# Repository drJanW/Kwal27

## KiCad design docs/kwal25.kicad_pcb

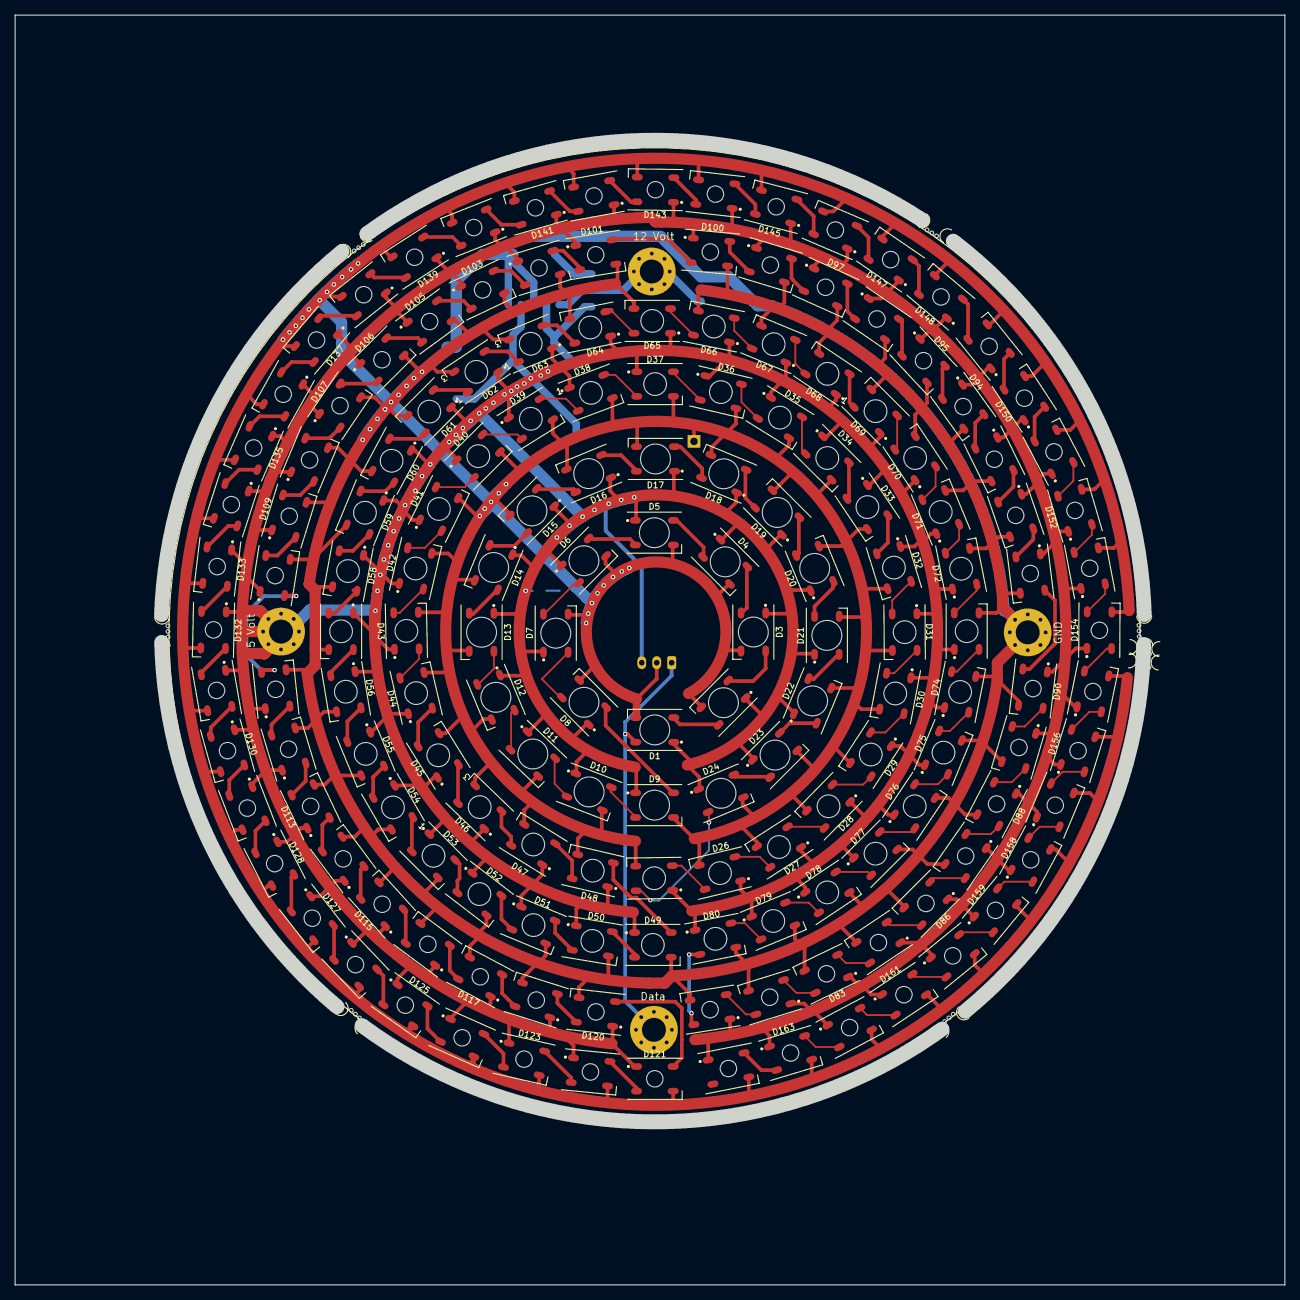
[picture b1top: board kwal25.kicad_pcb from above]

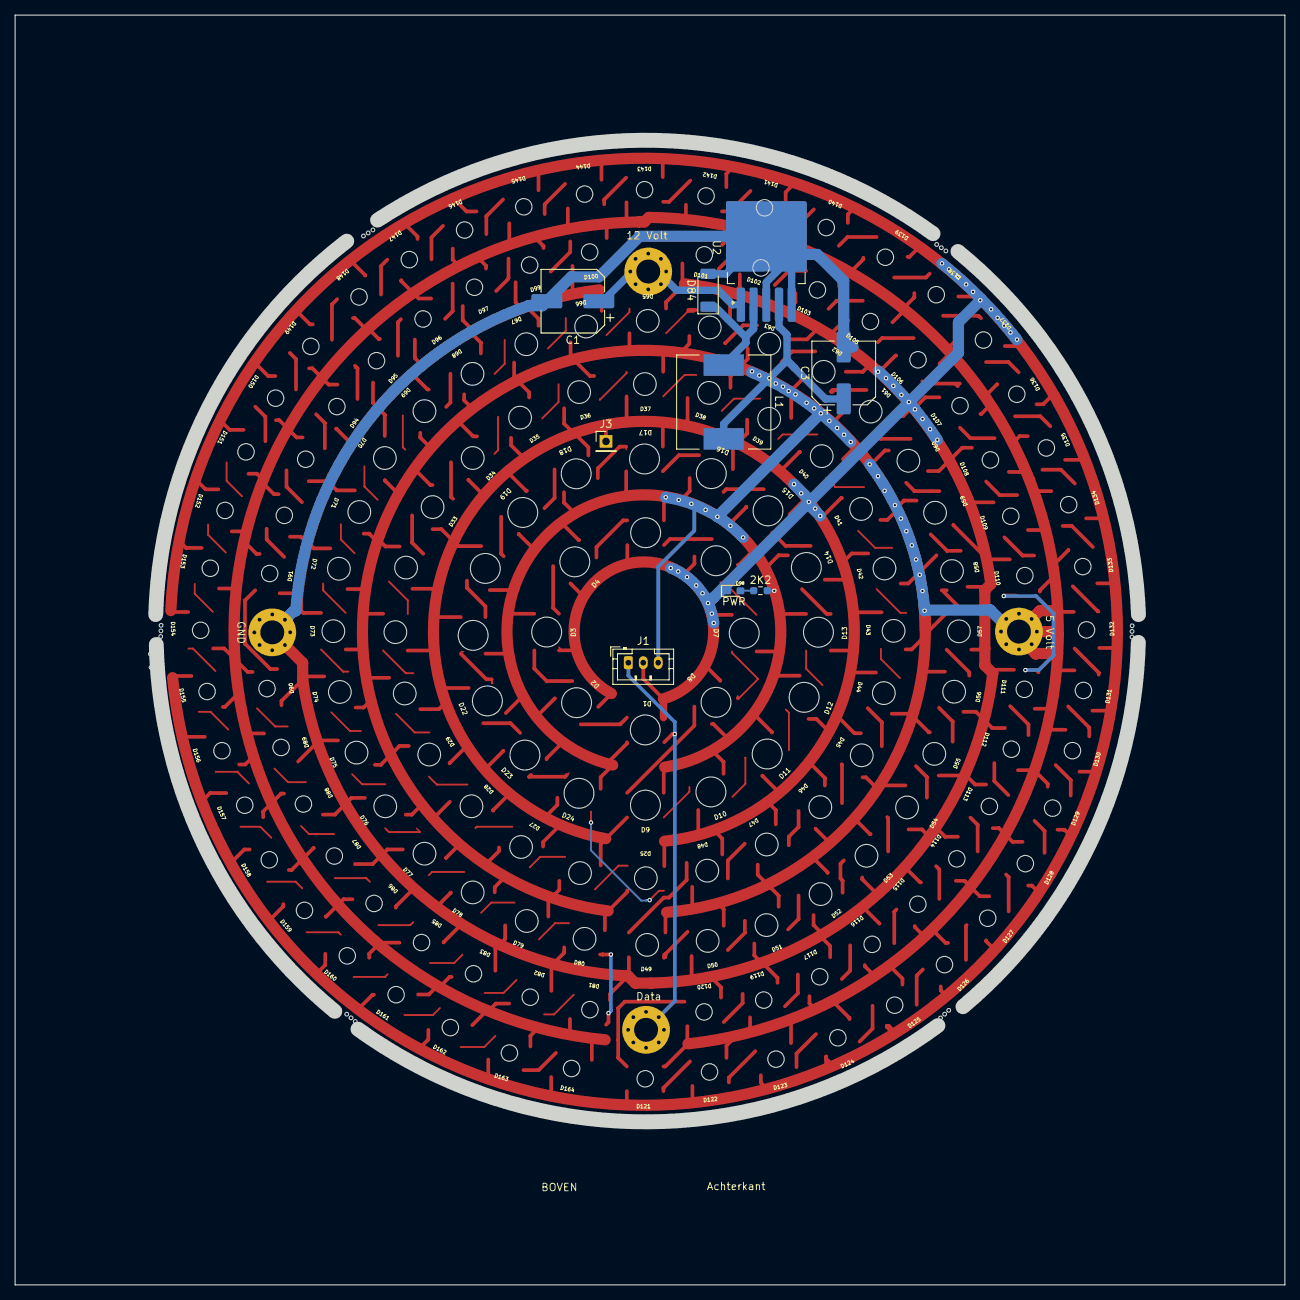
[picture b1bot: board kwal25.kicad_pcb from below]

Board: 2 copper layers, 170.0 x 170.0 mm, 181 parts (9 on the bottom side), 165 nets.

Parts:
C1: 100uF; CP_Elec_8x6.9
C3: 220 uF; CP_Elec_8x6.9
D1, D2, D3, D4, D5, D6, D7, D8, D9, D10, D11, D12, D13, D14, D15, D16, D17, D18, D19, D20, D21, D22, D23, D24: WS2812B; WS2812B_4_1
D25, D26, D27, D28, D29, D30, D31, D32, D33, D34, D35, D36, D37, D38, D39, D40, D41, D42, D43, D44, D45, D46, D47, D48, D49, D50, D51, D52, D53, D54, D55, D56, D57, D58, D59, D60, D61, D62, D63, D64, D65, D66, D67, D68, D69, D70, D71, D72, D73, D74, D75, D76, D77, D78, D79, D80: WS2812B; WS2812B_3_1
D81, D82, D83, D85, D86, D87, D88, D89, D90, D91, D92, D93, D94, D95, D96, D97, D99, D100, D101, D102, D103, D105, D106, D107, D108, D109, D110, D111, D112, D113, D114, D115, D116, D117, D119, D120, D121, D122, D123, D124, D125, D126, D127, D128, D129, D130, D131, D132, D133, D134, D135, D136, D137, D138, D139, D140, D141, D142, D143, D144, D145, D146, D147, D148, D149, D150, D151, D152, D153, D154, D155, D156, D157, D158, D159, D160, D161, D162, D163, D164: WS2812B; WS2812B_2_1
D84: SS34; D_SOD-128
D98: PWR; LED_0603_1608Metric_Pad1.05x0.95mm_HandSolder
H1: 12V; MountingHole_3.2mm_M3_Pad_Via
H2: Data; MountingHole_3.2mm_M3_Pad_Via
H3: Gnd; MountingHole_3.2mm_M3_Pad_Via
H4: 5V; MountingHole_3.2mm_M3_Pad_Via
J1: Conn_01x03; JST_PH_B3B-PH-K_1x03_P2.00mm_Vertical
J3: GND; PinHeader_1x01_P2.54mm_Vertical
L1: 470; L_12x12mm_H8mm
R1: 2K2; R_0603_1608Metric_Pad0.98x0.95mm_HandSolder
U2: LM2596S-5; TO-263-5_TabPin3
mouse-bite-1, mouse-bite-1#2, mouse-bite-1#3, mouse-bite-1#4, mouse-bite-1#5, mouse-bite-1#6, mouse-bite-1#7, mouse-bite-1#8: VAL**; mouse-bite-single-2mm-slot

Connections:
+5V: C3.1, D1.1 (VDD), D2.1 (VDD), D3.1 (VDD), D4.1 (VDD), D5.1 (VDD), D6.1 (VDD), D7.1 (VDD), D8.1 (VDD), D9.1 (VDD), D10.1 (VDD), D11.1 (VDD), D12.1 (VDD), D13.1 (VDD), D14.1 (VDD), D15.1 (VDD), D16.1 (VDD), D17.1 (VDD), D18.1 (VDD), D19.1 (VDD), D20.1 (VDD), D21.1 (VDD), D22.1 (VDD), D23.1 (VDD), D24.1 (VDD), D25.1 (VDD), D26.1 (VDD), D27.1 (VDD), D28.1 (VDD), D29.1 (VDD), D30.1 (VDD), D31.1 (VDD), D32.1 (VDD), D33.1 (VDD), D34.1 (VDD), D35.1 (VDD), D36.1 (VDD), D37.1 (VDD), D38.1 (VDD), D39.1 (VDD), D40.1 (VDD), D41.1 (VDD), D42.1 (VDD), D43.1 (VDD), D44.1 (VDD), D45.1 (VDD), D46.1 (VDD), D47.1 (VDD), D48.1 (VDD), D49.1 (VDD), D50.1 (VDD), D51.1 (VDD), D52.1 (VDD), D53.1 (VDD), D54.1 (VDD), D55.1 (VDD), D56.1 (VDD), D57.1 (VDD), D58.1 (VDD), D59.1 (VDD), D60.1 (VDD), D61.1 (VDD), D62.1 (VDD), D63.1 (VDD), D64.1 (VDD), D65.1 (VDD), D66.1 (VDD), D67.1 (VDD), D68.1 (VDD), D69.1 (VDD), D70.1 (VDD), D71.1 (VDD), D72.1 (VDD), D73.1 (VDD), D74.1 (VDD), D75.1 (VDD), D76.1 (VDD), D77.1 (VDD), D78.1 (VDD), D79.1 (VDD), D80.1 (VDD), D81.1 (VDD), D82.1 (VDD), D83.1 (VDD), D85.1 (VDD), D86.1 (VDD), D87.1 (VDD), D88.1 (VDD), D89.1 (VDD), D90.1 (VDD), D91.1 (VDD), D92.1 (VDD), D93.1 (VDD), D94.1 (VDD), D95.1 (VDD), D96.1 (VDD), D97.1 (VDD), D99.1 (VDD), D100.1 (VDD), D101.1 (VDD), D102.1 (VDD), D103.1 (VDD), D105.1 (VDD), D106.1 (VDD), D107.1 (VDD), D108.1 (VDD), D109.1 (VDD), D110.1 (VDD), D111.1 (VDD), D112.1 (VDD), D113.1 (VDD), D114.1 (VDD), D115.1 (VDD), D116.1 (VDD), D117.1 (VDD), D119.1 (VDD), D120.1 (VDD), D121.1 (VDD), D122.1 (VDD), D123.1 (VDD), D124.1 (VDD), D125.1 (VDD), D126.1 (VDD), D127.1 (VDD), D128.1 (VDD), D129.1 (VDD), D130.1 (VDD), D131.1 (VDD), D132.1 (VDD), D133.1 (VDD), D134.1 (VDD), D135.1 (VDD), D136.1 (VDD), D137.1 (VDD), D138.1 (VDD), D139.1 (VDD), D140.1 (VDD), D141.1 (VDD), D142.1 (VDD), D143.1 (VDD), D144.1 (VDD), D145.1 (VDD), D146.1 (VDD), D147.1 (VDD), D148.1 (VDD), D149.1 (VDD), D150.1 (VDD), D151.1 (VDD), D152.1 (VDD), D153.1 (VDD), D154.1 (VDD), D155.1 (VDD), D156.1 (VDD), D157.1 (VDD), D158.1 (VDD), D159.1 (VDD), D160.1 (VDD), D161.1 (VDD), D162.1 (VDD), D163.1 (VDD), D164.1 (VDD), H4.1, J1.3, L1.2, R1.1, U2.4 (FB)
+12V: C1.1, H1.1, U2.1 (VIN)
Data: D1.4 (DIN), H2.1, J1.1
GND: C1.2, C3.2, D1.3 (VSS), D2.3 (VSS), D3.3 (VSS), D4.3 (VSS), D5.3 (VSS), D6.3 (VSS), D7.3 (VSS), D8.3 (VSS), D9.3 (VSS), D10.3 (VSS), D11.3 (VSS), D12.3 (VSS), D13.3 (VSS), D14.3 (VSS), D15.3 (VSS), D16.3 (VSS), D17.3 (VSS), D18.3 (VSS), D19.3 (VSS), D20.3 (VSS), D21.3 (VSS), D22.3 (VSS), D23.3 (VSS), D24.3 (VSS), D25.3 (VSS), D26.3 (VSS), D27.3 (VSS), D28.3 (VSS), D29.3 (VSS), D30.3 (VSS), D31.3 (VSS), D32.3 (VSS), D33.3 (VSS), D34.3 (VSS), D35.3 (VSS), D36.3 (VSS), D37.3 (VSS), D38.3 (VSS), D39.3 (VSS), D40.3 (VSS), D41.3 (VSS), D42.3 (VSS), D43.3 (VSS), D44.3 (VSS), D45.3 (VSS), D46.3 (VSS), D47.3 (VSS), D48.3 (VSS), D49.3 (VSS), D50.3 (VSS), D51.3 (VSS), D52.3 (VSS), D53.3 (VSS), D54.3 (VSS), D55.3 (VSS), D56.3 (VSS), D57.3 (VSS), D58.3 (VSS), D59.3 (VSS), D60.3 (VSS), D61.3 (VSS), D62.3 (VSS), D63.3 (VSS), D64.3 (VSS), D65.3 (VSS), D66.3 (VSS), D67.3 (VSS), D68.3 (VSS), D69.3 (VSS), D70.3 (VSS), D71.3 (VSS), D72.3 (VSS), D73.3 (VSS), D74.3 (VSS), D75.3 (VSS), D76.3 (VSS), D77.3 (VSS), D78.3 (VSS), D79.3 (VSS), D80.3 (VSS), D81.3 (VSS), D82.3 (VSS), D83.3 (VSS), D84.2 (A), D85.3 (VSS), D86.3 (VSS), D87.3 (VSS), D88.3 (VSS), D89.3 (VSS), D90.3 (VSS), D91.3 (VSS), D92.3 (VSS), D93.3 (VSS), D94.3 (VSS), D95.3 (VSS), D96.3 (VSS), D97.3 (VSS), D98.1 (K), D99.3 (VSS), D100.3 (VSS), D101.3 (VSS), D102.3 (VSS), D103.3 (VSS), D105.3 (VSS), D106.3 (VSS), D107.3 (VSS), D108.3 (VSS), D109.3 (VSS), D110.3 (VSS), D111.3 (VSS), D112.3 (VSS), D113.3 (VSS), D114.3 (VSS), D115.3 (VSS), D116.3 (VSS), D117.3 (VSS), D119.3 (VSS), D120.3 (VSS), D121.3 (VSS), D122.3 (VSS), D123.3 (VSS), D124.3 (VSS), D125.3 (VSS), D126.3 (VSS), D127.3 (VSS), D128.3 (VSS), D129.3 (VSS), D130.3 (VSS), D131.3 (VSS), D132.3 (VSS), D133.3 (VSS), D134.3 (VSS), D135.3 (VSS), D136.3 (VSS), D137.3 (VSS), D138.3 (VSS), D139.3 (VSS), D140.3 (VSS), D141.3 (VSS), D142.3 (VSS), D143.3 (VSS), D144.3 (VSS), D145.3 (VSS), D146.3 (VSS), D147.3 (VSS), D148.3 (VSS), D149.3 (VSS), D150.3 (VSS), D151.3 (VSS), D152.3 (VSS), D153.3 (VSS), D154.3 (VSS), D155.3 (VSS), D156.3 (VSS), D157.3 (VSS), D158.3 (VSS), D159.3 (VSS), D160.3 (VSS), D161.3 (VSS), D162.3 (VSS), D163.3 (VSS), D164.3 (VSS), H3.1, J1.2, J3.1, U2.3 (GND), U2.5 (~ON/OFF)
unnamed: D1.2 (DOUT), D2.4 (DIN)
unnamed: D2.2 (DOUT), D3.4 (DIN)
unnamed: D3.2 (DOUT), D4.4 (DIN)
unnamed: D4.2 (DOUT), D5.4 (DIN)
unnamed: D5.2 (DOUT), D6.4 (DIN)
unnamed: D6.2 (DOUT), D7.4 (DIN)
unnamed: D7.2 (DOUT), D8.4 (DIN)
unnamed: D8.2 (DOUT), D9.4 (DIN)
unnamed: D9.2 (DOUT), D10.4 (DIN)
unnamed: D10.2 (DOUT), D11.4 (DIN)
unnamed: D11.2 (DOUT), D12.4 (DIN)
unnamed: D12.2 (DOUT), D13.4 (DIN)
unnamed: D13.2 (DOUT), D14.4 (DIN)
unnamed: D14.2 (DOUT), D15.4 (DIN)
unnamed: D15.2 (DOUT), D16.4 (DIN)
unnamed: D16.2 (DOUT), D17.4 (DIN)
unnamed: D17.2 (DOUT), D18.4 (DIN)
unnamed: D18.2 (DOUT), D19.4 (DIN)
unnamed: D19.2 (DOUT), D20.4 (DIN)
unnamed: D20.2 (DOUT), D21.4 (DIN)
unnamed: D21.2 (DOUT), D22.4 (DIN)
unnamed: D22.2 (DOUT), D23.4 (DIN)
unnamed: D23.2 (DOUT), D24.4 (DIN)
unnamed: D24.2 (DOUT), D25.4 (DIN)
unnamed: D25.2 (DOUT), D26.4 (DIN)
unnamed: D26.2 (DOUT), D27.4 (DIN)
unnamed: D27.2 (DOUT), D28.4 (DIN)
unnamed: D28.2 (DOUT), D29.4 (DIN)
unnamed: D29.2 (DOUT), D30.4 (DIN)
unnamed: D30.2 (DOUT), D31.4 (DIN)
unnamed: D31.2 (DOUT), D32.4 (DIN)
unnamed: D32.2 (DOUT), D33.4 (DIN)
unnamed: D33.2 (DOUT), D34.4 (DIN)
unnamed: D34.2 (DOUT), D35.4 (DIN)
unnamed: D35.2 (DOUT), D36.4 (DIN)
unnamed: D36.2 (DOUT), D37.4 (DIN)
unnamed: D37.2 (DOUT), D38.4 (DIN)
unnamed: D38.2 (DOUT), D39.4 (DIN)
unnamed: D39.2 (DOUT), D40.4 (DIN)
unnamed: D40.2 (DOUT), D41.4 (DIN)
unnamed: D41.2 (DOUT), D42.4 (DIN)
unnamed: D42.2 (DOUT), D43.4 (DIN)
unnamed: D43.2 (DOUT), D44.4 (DIN)
unnamed: D44.2 (DOUT), D45.4 (DIN)
unnamed: D45.2 (DOUT), D46.4 (DIN)
unnamed: D46.2 (DOUT), D47.4 (DIN)
unnamed: D47.2 (DOUT), D48.4 (DIN)
unnamed: D48.2 (DOUT), D49.4 (DIN)
unnamed: D49.2 (DOUT), D50.4 (DIN)
unnamed: D50.2 (DOUT), D51.4 (DIN)
unnamed: D51.2 (DOUT), D52.4 (DIN)
unnamed: D52.2 (DOUT), D53.4 (DIN)
unnamed: D53.2 (DOUT), D54.4 (DIN)
unnamed: D54.2 (DOUT), D55.4 (DIN)
unnamed: D55.2 (DOUT), D56.4 (DIN)
unnamed: D56.2 (DOUT), D57.4 (DIN)
unnamed: D57.2 (DOUT), D58.4 (DIN)
unnamed: D58.2 (DOUT), D59.4 (DIN)
unnamed: D59.2 (DOUT), D60.4 (DIN)
unnamed: D60.2 (DOUT), D61.4 (DIN)
unnamed: D61.2 (DOUT), D62.4 (DIN)
unnamed: D62.2 (DOUT), D63.4 (DIN)
unnamed: D63.2 (DOUT), D64.4 (DIN)
unnamed: D64.2 (DOUT), D65.4 (DIN)
unnamed: D65.2 (DOUT), D66.4 (DIN)
unnamed: D66.2 (DOUT), D67.4 (DIN)
unnamed: D67.2 (DOUT), D68.4 (DIN)
unnamed: D68.2 (DOUT), D69.4 (DIN)
unnamed: D69.2 (DOUT), D70.4 (DIN)
unnamed: D70.2 (DOUT), D71.4 (DIN)
unnamed: D71.2 (DOUT), D72.4 (DIN)
unnamed: D72.2 (DOUT), D73.4 (DIN)
unnamed: D73.2 (DOUT), D74.4 (DIN)
unnamed: D74.2 (DOUT), D75.4 (DIN)
unnamed: D75.2 (DOUT), D76.4 (DIN)
unnamed: D76.2 (DOUT), D77.4 (DIN)
unnamed: D77.2 (DOUT), D78.4 (DIN)
unnamed: D78.2 (DOUT), D79.4 (DIN)
unnamed: D79.2 (DOUT), D80.4 (DIN)
unnamed: D80.2 (DOUT), D81.4 (DIN)
unnamed: D81.2 (DOUT), D82.4 (DIN)
unnamed: D82.2 (DOUT), D83.4 (DIN)
unnamed: D83.2 (DOUT), D85.4 (DIN)
unnamed: D84.1 (K), L1.1, U2.2 (OUT)
unnamed: D85.2 (DOUT), D86.4 (DIN)
unnamed: D86.2 (DOUT), D87.4 (DIN)
unnamed: D87.2 (DOUT), D88.4 (DIN)
unnamed: D88.2 (DOUT), D89.4 (DIN)
unnamed: D89.2 (DOUT), D90.4 (DIN)
unnamed: D90.2 (DOUT), D91.4 (DIN)
unnamed: D91.2 (DOUT), D92.4 (DIN)
unnamed: D92.2 (DOUT), D93.4 (DIN)
unnamed: D93.2 (DOUT), D94.4 (DIN)
unnamed: D94.2 (DOUT), D95.4 (DIN)
unnamed: D95.2 (DOUT), D96.4 (DIN)
unnamed: D96.2 (DOUT), D97.4 (DIN)
unnamed: D97.2 (DOUT), D99.4 (DIN)
unnamed: D98.2 (A), R1.2
unnamed: D99.2 (DOUT), D100.4 (DIN)
unnamed: D100.2 (DOUT), D101.4 (DIN)
unnamed: D101.2 (DOUT), D102.4 (DIN)
unnamed: D102.2 (DOUT), D103.4 (DIN)
unnamed: D103.2 (DOUT), D105.4 (DIN)
unnamed: D105.2 (DOUT), D106.4 (DIN)
unnamed: D106.2 (DOUT), D107.4 (DIN)
unnamed: D107.2 (DOUT), D108.4 (DIN)
unnamed: D108.2 (DOUT), D109.4 (DIN)
unnamed: D109.2 (DOUT), D110.4 (DIN)
unnamed: D110.2 (DOUT), D111.4 (DIN)
unnamed: D111.2 (DOUT), D112.4 (DIN)
unnamed: D112.2 (DOUT), D113.4 (DIN)
unnamed: D113.2 (DOUT), D114.4 (DIN)
unnamed: D114.2 (DOUT), D115.4 (DIN)
unnamed: D115.2 (DOUT), D116.4 (DIN)
unnamed: D116.2 (DOUT), D117.4 (DIN)
unnamed: D117.2 (DOUT), D119.4 (DIN)
unnamed: D119.2 (DOUT), D120.4 (DIN)
unnamed: D120.2 (DOUT), D121.4 (DIN)
unnamed: D121.2 (DOUT), D122.4 (DIN)
unnamed: D122.2 (DOUT), D123.4 (DIN)
unnamed: D123.2 (DOUT), D124.4 (DIN)
unnamed: D124.2 (DOUT), D125.4 (DIN)
unnamed: D125.2 (DOUT), D126.4 (DIN)
unnamed: D126.2 (DOUT), D127.4 (DIN)
unnamed: D127.2 (DOUT), D128.4 (DIN)
unnamed: D128.2 (DOUT), D129.4 (DIN)
unnamed: D129.2 (DOUT), D130.4 (DIN)
unnamed: D130.2 (DOUT), D131.4 (DIN)
unnamed: D131.2 (DOUT), D132.4 (DIN)
unnamed: D132.2 (DOUT), D133.4 (DIN)
unnamed: D133.2 (DOUT), D134.4 (DIN)
unnamed: D134.2 (DOUT), D135.4 (DIN)
unnamed: D135.2 (DOUT), D136.4 (DIN)
unnamed: D136.2 (DOUT), D137.4 (DIN)
unnamed: D137.2 (DOUT), D138.4 (DIN)
unnamed: D138.2 (DOUT), D139.4 (DIN)
unnamed: D139.2 (DOUT), D140.4 (DIN)
unnamed: D140.2 (DOUT), D141.4 (DIN)
unnamed: D141.2 (DOUT), D142.4 (DIN)
unnamed: D142.2 (DOUT), D143.4 (DIN)
unnamed: D143.2 (DOUT), D144.4 (DIN)
unnamed: D144.2 (DOUT), D145.4 (DIN)
unnamed: D145.2 (DOUT), D146.4 (DIN)
unnamed: D146.2 (DOUT), D147.4 (DIN)
unnamed: D147.2 (DOUT), D148.4 (DIN)
unnamed: D148.2 (DOUT), D149.4 (DIN)
unnamed: D149.2 (DOUT), D150.4 (DIN)
unnamed: D150.2 (DOUT), D151.4 (DIN)
unnamed: D151.2 (DOUT), D152.4 (DIN)
unnamed: D152.2 (DOUT), D153.4 (DIN)
unnamed: D153.2 (DOUT), D154.4 (DIN)
unnamed: D154.2 (DOUT), D155.4 (DIN)
unnamed: D155.2 (DOUT), D156.4 (DIN)
unnamed: D156.2 (DOUT), D157.4 (DIN)
unnamed: D157.2 (DOUT), D158.4 (DIN)
unnamed: D158.2 (DOUT), D159.4 (DIN)
unnamed: D159.2 (DOUT), D160.4 (DIN)
unnamed: D160.2 (DOUT), D161.4 (DIN)
unnamed: D161.2 (DOUT), D162.4 (DIN)
unnamed: D162.2 (DOUT), D163.4 (DIN)
unnamed: D163.2 (DOUT), D164.4 (DIN)

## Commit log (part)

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2026-01-27 260127A: baseline before TimerManager refactor (token support, global instance)
2026-01-27 260127A: timers global migration WIP
2026-01-27 260127A: TimerManager cleanup - T2,T4,T9 done
2026-01-28 SDManager refactor tested - 26/27 checks passed
2026-01-28 PRTClock: eliminate instance() singleton, use global prtClock
2026-01-29 LightManager: remove singleton, use global lightManager
2026-01-29 WiFiManager: remove status wrapper, align state access
2026-01-31 Clarify Copilot prompt and update rename todo
2026-01-31 Update rename todo and add v2 naming docs
2026-01-31 Light Store to Catalog/Table
2026-02-01 Docs: Store to Catalog/Table
2026-02-02 Rename: phase G terminology + calendar selector fix
2026-02-02 Cleanup: remove shim files
2026-02-02 Rename: manager folders to controller
2026-02-02 na renames
2026-02-04 NAS CSV server port 8081, nasstart.ps1 one-click
2026-02-05 Enable timestamps and update headers
2026-02-05 Rename BootMaster to BootManager for consistency
2026-02-06 Boot: welcome after calendar ready
2026-02-06 260206N: HTTP OTA upload, deploy.ps1 MARMER via HTTP, legacy OTA behouden
2026-02-07 260207D: b12 Stevens power law for lux brightness curve
2026-02-07 Move and rename AUDIO_GAIN_SEMANTICS.md -> docs/coding_tech/audio_volume_semantics.md
    - Renamed file: gain→volume in filename
    - Updated all prose: gain→volume, modifier→fraction
    - Updated getter/setter names to match current code (getVolumeShiftedHi, setVolumeWebShift)
    - Added note about pending variable renames (glossary cross-ref)
    - Version bumped to 260207F
2026-02-08 Custom canvas color picker - fixes Android WebView browsers (260208B)
    - New colorpicker.js: canvas-based HSV picker (touch + mouse)
    - colors.js: replace <input type=color> with custom picker
    - index.html: add colorpicker-modal (canvas, hue bar, hex input, preview)
    - styles.css: add .cp-* styles with touch-action:none
    - main.js: init Kwal.colorpicker before Kwal.colors
    - build.ps1: add colorpicker.js to module list
2026-02-09 260209B - Weather retry, health panel enhancements, speak temp guard
    - Weather fetch: two-phase boot retry (14x, 1.5× growth) then hourly periodic
    - Weather periodic failure: guard clearWeather() to preserve stale data
    - Health panel: show RTC temperature inline with RTC checkmark
    - Health panel: show calendar date (dd-mm) inline with Calendar checkmark
    - Speak temperature: limit to >75°C only, rename sayTemperature → sayRTCtemperature
    - Version bump: firmware + WebGUI 260209B
2026-02-10 color/pattern timer change: 5.8h color, 4.9h pattern, health log 40min
2026-02-11 260211B: fix OOM crash, add NAS health monitoring, timer-based voting
    Crash fix (OOM during audio+webserver):
    - WiFiBoot: defer NasBackup::checkHealth() to 30s one-shot timer
    (avoids 9th TCP connection while 8 CSV downloads still in TIME_WAIT)
    - LogBuffer: reduce 16KB -> 12KB (16KB was marginal with NasBackup TCP)
    NAS health monitoring (new SC_NAS status component):
    - AlertState: SC_NAS in enum, reset() inits NOT_OK, setNasStatus/isNasOk
2026-02-11 MP3 grid UX redesign + single-dir theme box + box name display
    MP3 Grid:
    - Remove header, replace play icon with close icon
    - Click DIR label/value: set single-dir theme box
    - Click FILE label/value: play that file
    - Double-click canvas: play file
    - Grid cell size 3 -> 5px, wrap height 300 -> 480px
2026-02-11 Make volume and brightness sliders linear (remove quadratic curve)
    - Removed Kwal.sliderToValue/valueToSlider calls from audio.js and brightness.js
    - Slider position now equals percentage directly
    - WebGUI 260211K, uploaded to both HOUT and MARMER
2026-02-12 260212D: rename getEffectiveVolume -> getVolumeMultiplier
    - AudioShiftTable: getEffectiveVolume() -> getVolumeMultiplier()
    - AudioRun: effectiveVolume -> volumeMultiplier, scaledVolume -> shiftedHi
    - Updated audio_volume_semantics.md references
    - Version bumped to 260212D
2026-02-12 deploy: auto-sync updated CSVs from NAS to sdroot before deploy; updated light_patterns.csv with patterns 27-30
2026-02-12 Early RTC read, clean log timestamps, encapsulate RTCController
2026-02-12 NAS health: escalating retry (2min x3) + WiFi reconnect recovery
2026-02-13 theme_boxes: add dir 075 to DEFAULT, ALLBIRDS, BIRDS7
2026-02-15 wifi.txt: IP in config, scripts stripped, upload_wifi.ps1 added, manual updated
2026-02-15 260215F: default slider positions brightness=60% audio=70%, copilot-instructions device roles
2026-02-16 TTS: random NL/BE voices, r=-2 tempo, theme box timing quickfix
2026-02-16 MARMER synced: web+csv+firmware 260216J deployed to both devices
2026-02-17 Add SD endpoints: list, delete, upload-to-subdir, syncdir
    - /api/sd/list?path=/NNN — list files in directory
    - /api/sd/delete?path=/NNN/MMM.mp3 — delete file (no index update)
    - /api/sd/upload?path=/NNN — upload file to subdirectory
    - /api/sd/syncdir?dir=NNN — deferred index rebuild preserving votes
    - SDController::syncDirectory() — vote-preserving scan variant
    - SDBoot::requestSyncDir() — timer-deferred mechanism
2026-02-17 Remove isSdBusy guard from list endpoint - lockSD handles it
    Allows sync_mp3.ps1 to scan dirs during audio playback.
    Also: retry logic in sync_mp3.ps1 for delete/upload.
    Firmware 260217E
2026-02-17 Fix routeFileDownload: add isSdBusy guard + lockSD + read to stream
    - routeFileDownload now checks isSdBusy, reads file under lockSD into
    AsyncResponseStream, then sends from RAM. No async SD file handle.
    - Max 64KB file size guard to protect heap.
    - sync_mp3.ps1: retry helper for binary file downloads (SD busy 409).
    - Removed unused <memory> include.
2026-02-18 260218E: SD fallback WebGUI, pattern fallback, boot version print
2026-02-18 260218N: SDBoot rebuild log verduidelijkt (votes will be preserved)
2026-02-19 sync MP3 naar 188+189, beide draaien zelfde firmware en MP3 set
2026-02-19 260219E: audio source tags, fade format, boot log alignment, deploy.ps1 simplify, TTS null fix
2026-02-20 260220B: restore brightnessLo 70
2026-02-25 chore: full workspace commit incl FAQ cleanup
2026-02-26 audioplus: unified expiry for all web audio overrides (volume+intervals+silence), default 13hr
2026-02-26 audioplus: web audio intervals, silence, mute + WebGUI sliders (v260226A)
2026-02-26 Audio preemption architectural recovery + WebAudio interval logging
2026-02-27 Architecture cleanup: 38 violations + 27 warnings → 0
    - Created lib/SdFileAccess as shared lib (SD lock, file I/O, path utils)
    - Moved AudioState.h/.cpp from AudioManager to Globals (shared state)
    - Moved SDSettings.h, SDBusyGuard.h, SdPathUtils to SdFileAccess
    - Broke Clock↔WiFi cycle via ContextController mediator API
    - Removed unused cross-controller includes (WiFi from PlaySentence, Sensor from LightController)
    - Removed FastLED.h from AlertPolicy.h
2026-02-28 B10: Lux calibration plan - terminology fix + pattern corrections
    - copilot-instructions.md: add colors/colors's terminology rules
    (colors = palette, NOT plural of color; plural = colors's)
    - plan_b10_lux_calibration.md: replace all colorSet with colors
    - Add per-pattern correction factor (v2, section 3g)
    - FIFO bumped to 500 samples, 500 seeds (high→low lux order)
    - Struct simplified to 10 bytes (normalized luxBrightness, numeric IDs)
2026-03-02 Add plan_snb.md reference doc, resolve E1+Q4 in tracker
2026-03-02 Resolve all errors: E8 deferred, E9 not an error, E10 resolved by SNB ordering
2026-03-02 Rename colorsCorrection/patternCorrection to cnf/pnf, add PNF stub to Part 1
2026-03-02 ensurePnf: stub 0→1.0f in memory after CSV load, simplify pnf() accessor
2026-03-04 260303A: Part 2 lux calibration firmware — LuxCalibration module, LuxCalRoutes (7 endpoints), sample capture in cb_measureLux, pre-clamp brightness storage
2026-03-04 260304F BootSequencer: declarative manifest-driven boot replacing boolean-flag chain
2026-03-05 260304H: WebGUI icon-only UI, main screen icons, vote score centered
2026-03-05 260305D: serial log cleanup phase 2
2026-03-06 TV simulator plan v3: simplified to 3 functions, 0 guards, 0 custom render, ~91 lines
2026-03-07 260307B: Add PSRAM min monitoring to status log, health API, and WebGUI
2026-03-07 260307D: tvMode in SSE state event, TV UI persists across reconnects
2026-03-08 260308A: Skip ping.wav load when no distance sensor — saves ~27KB heap
2026-03-09 260309B: fix grid search ranges, auto-fit accept flow, pushLuxcalFit SSE, accept icon styling
2026-03-10 260310F: TV SSE load order fix, grid shift range 90, fitShiftLimit const, hasLuxSensor quote fix
2026-03-11 260311C: luxcal normalization, quadratic slider, observed luxMax, OTA icon, timestamped CSV download
2026-03-13 Update A3 todo: mark SDController cleanup as done, keep remaining items
2026-03-13 260313D: Replace Stevens power law with exponential saturation model, Gauss-Newton fit, R2 metric, restore luxMax high-water mark
2026-03-13 audioShifts.csv: add speakMin/Max fragmentMin/Max columns
2026-03-16 260316B: dark mode - click lightbulb to toggle LEDs off/on
2026-03-16 260316F: dark mode log, red frag slider, bezoeker howto rewrite
2026-03-16 260316K: NAS CSVs download to SD root, remove /nas/ overlay
2026-03-16 Fix audio header layout: voting+fragment-id fit on one line
2026-03-17 260317D/L: Cal Lux - seeds-only fit for old row, clear keeps seeds, reset icon for defaults
2026-03-19 260319A: sync headers (54), update readmes (14), update coding_tech docs (9), delete rules.txt, fix luxcal wis
2026-04-07 docs: add free-text tts limits
2026-04-07 docs: remove redundant active flag from free-text TTS data model
2026-04-07 docs: specify icon-based UI pattern for free-text TTS
2026-04-09 260409G: TTS-to-SD cache feature + docs update
    - Free text TTS: download VoiceRSS MP3 to /127/000.mp3, play via PlayFragment
    - Repeat plays from SD cache (no repeated HTTP calls)
    - Architecture fix: web handler no longer blocks on HTTP (deferred to timer)
    - Duration calc: filesize-based with configurable factor (3.0)
    - New globals: ttsCacheDirIndex, ttsCacheFileIndex, ttsCacheDurationFactor
    - Deleted plan_web_free_text_tts.txt (implemented)
2026-04-09 260409K: Calendar TTS cached to /127/001.mp3, deferred download callback
2026-04-12 plan admin settings modal
2026-05-30 260413A admin settings routes
2026-06-04 demo: tts_todo.csv queue + audio sourcing lijst
2026-06-04 260604C: TtsTodoQueue self-consuming render queue (PlaySentence dirIndex param, boot hook); fix AdminRoutes stray block
2026-06-05 v260605S - Demo bugfixes (audio scale, onweer, colors, spectrum speed, tv-sim audio, reboot reset)
2026-06-08 260608C: demo live TTS voice=Bram tempo=-1, skip ch19 bij sunrise=0, stop audio+alertRGB bij demo start
2026-06-08 260608G-K: DemoRun cleanup, sunrise HTTPS fix, live TTS timing fix, chapter 16 removed
2026-06-14 v260614A: plan_ringshow.md — RingShow architecture, replace Spectrum with RingRenderer
